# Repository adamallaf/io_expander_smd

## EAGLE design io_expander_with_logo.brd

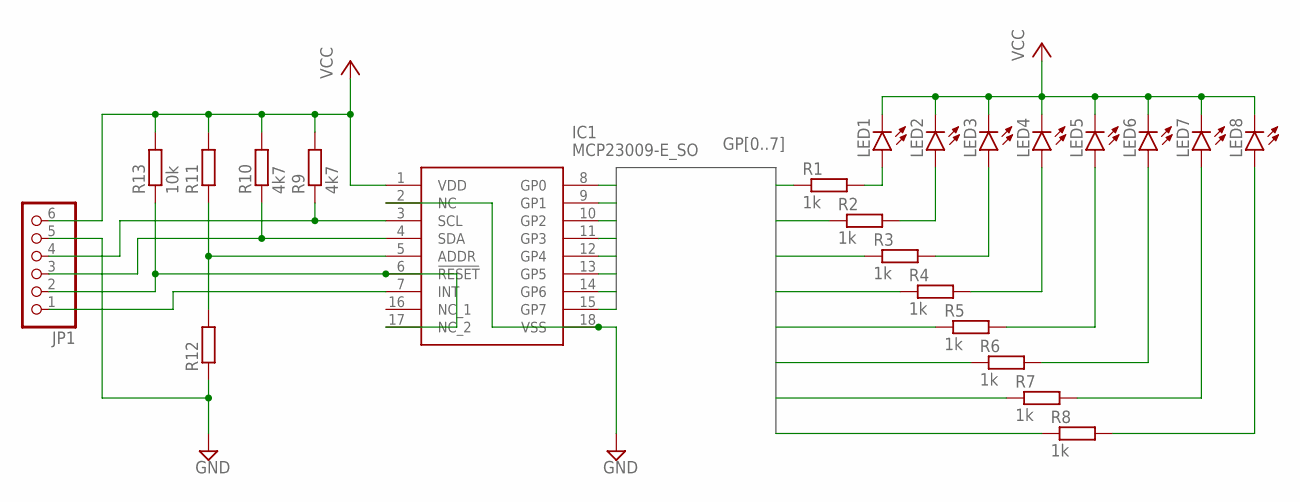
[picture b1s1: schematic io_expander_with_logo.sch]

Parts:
IC1: MCP23009-E_SO; SOIC127P1030X265-18N
JP1: PINHD-1X6; 1X06
LED1, LED2, LED3, LED4, LED5, LED6, LED7, LED8: LEDCHIP-LED0805; CHIP-LED0805
R1, R2, R3, R4, R5, R6, R7, R8: 1k; R0805
R9, R10: 4k7; R0805
R11, R12: R-EU_R0805; R0805
R13: 10k; R0805

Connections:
GND: IC1.2 (NC), IC1.18 (VSS), JP1.5, R12.1
GP0: IC1.8 (GP0), R1.1
GP1: IC1.9 (GP1), R2.1
GP2: IC1.10 (GP2), R3.1
GP3: IC1.11 (GP3), R4.1
GP4: IC1.12 (GP4), R5.1
GP5: IC1.13 (GP5), R6.1
GP6: IC1.14 (GP6), R7.1
GP7: IC1.15 (GP7), R8.1
unnamed: IC1.5 (ADDR), R11.1, R12.2
unnamed: IC1.3 (SCL), JP1.4, R9.1
unnamed: IC1.4 (SDA), JP1.3, R10.1
unnamed: IC1.6 (!RESET), IC1.17 (NC_2), JP1.2, R13.1
unnamed: IC1.7 (INT), JP1.1
unnamed: LED1.A, R1.2
unnamed: LED2.A, R2.2
unnamed: LED3.A, R3.2
unnamed: LED4.A, R4.2
unnamed: LED5.A, R5.2
unnamed: LED6.A, R6.2
unnamed: LED7.A, R7.2
unnamed: LED8.A, R8.2
VCC: IC1.1 (VDD), JP1.6, LED1.C, LED2.C, LED3.C, LED4.C, LED5.C, LED6.C, LED7.C, LED8.C, R9.2, R10.2, R11.2, R13.2

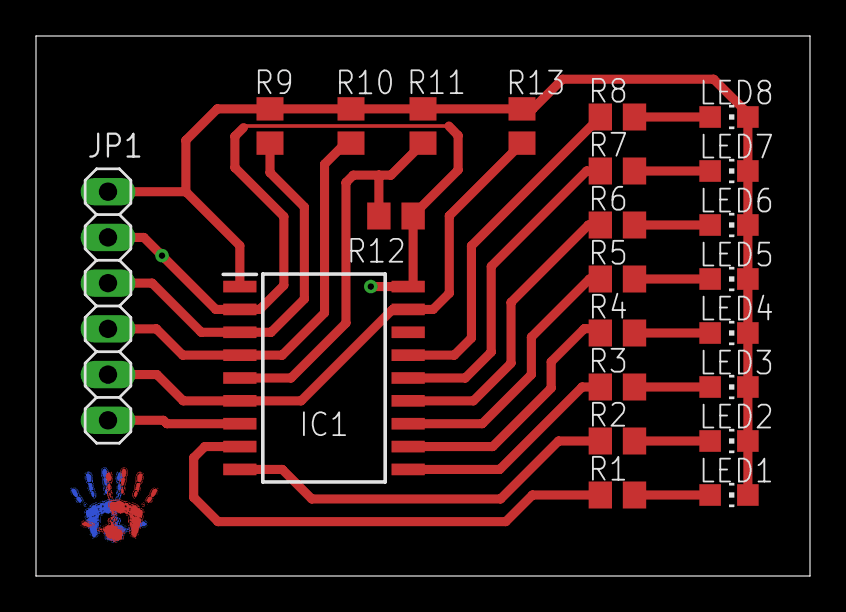
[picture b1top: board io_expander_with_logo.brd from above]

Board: 2 copper layers, 43.0 x 30.0 mm, 25 parts (1 on the bottom side), 23 nets.

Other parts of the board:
U$1, U$2: 2313_B

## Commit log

2020-02-13 Initialized git, added PCB project in eagle & gerber files
2020-02-13 Added PCB images
2020-02-13 Added top layer image
2020-02-17 Added hand logo
